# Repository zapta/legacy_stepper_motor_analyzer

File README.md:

# Legacy Stepper Motor Analyzer

<span style="color:red"><b>
NOTE: This is the legacy STM32 based design which was  replaced by the single board, Raspberry Pi Pico design at https://github.com/zapta/simple_stepper_motor_analyzer.</b></span>

&nbsp;

https://github.com/zapta/legacy_stepper_motor_analyzer

&nbsp;

&nbsp;

## Demonstration

Michael from the Teaching Tech youtube channel made [a great video explaining how stepper motors work](https://youtu.be/4iII25DGIdA) and used the Simple Stepper Motor Analyzer for some of the demonstrations. 

&nbsp;

## Highlights
* Low cost and minimalist DYI hardware design.
* Standalone. Doesn't require a computer to operate.
* Analyzes the stepper motor signals in the actual system (e.g. a 3D printer).
* Galvanically isolated current sensors. Does not interfere with the operating equipment, even when its turned off.
* Easy to connect using a pair 4 wire pass through connectors.
* Intuitive user interface with color display and a capacitive touch.
* Microstepping resolution of 1% of a full step.
* Provides momentary readings, signal patterns, and statistical measurements.
* Hardware and software are open sourced with a generous license.
* Based on free tools (Kicad, platformio, LVGL, STM32Duino).
* Can be easily customized (new featured, cost reduction, data link to a computer, etc).
* Powered 5VDC, 200ma via a USB-C connector.

## Overview
Diagnosing the operation of stepper motor in 3D printers and CNC machines used to require stepper motor analyzers that costs thousands of dollar. Not anymore! The Simple Stepper Analyzer ('Analyzer' in short) brings these capabilities to every maker for a tiny fraction of the price and with a minimalist DIY electronic design that leaves the heavy lifting to the firmware.

The Analyzer is self contained, has two 4-wires pass-through connectors connecting the stepper motor, is powered from a common 5V charger with a micro USB cable, provides a simple to use graphical user interface with a 3.5" color touch screen, and provides a plethora of stepper motor measurements.

The Analyzer is provided to the community as a public domain reference design that can be built and used as is, or be customized with additional features or for a lower cost as desired. The hardware and firmware come with a liberal open source license (CC0) that allows commercial usages and doesn't require code source code sharing.

---
## Disclaimer
THE DESIGN IS PROVIDED "AS IS", WITHOUT WARRANTY OF ANY KIND, EXPRESS OR IMPLIED, INCLUDING BUT NOT LIMITED TO THE WARRANTIES OF MERCHANTABILITY, FITNESS FOR A PARTICULAR PURPOSE AND NONINFRINGEMENT. IN NO EVENT SHALL THE AUTHORS OR COPYRIGHT HOLDERS BE LIABLE FOR ANY CLAIM, DAMAGES OR OTHER LIABILITY, WHETHER IN AN ACTION OF CONTRACT, TORT OR OTHERWISE, ARISING FROM, OUT OF OR IN CONNECTION WITH THE DESIGN OR THE USE OR OTHER DEALINGS IN THE DESIGN.

---

## Alternative construction option (enclosed case)
**NOTE:** This pages outlines the open base construction options which is easier and straight forward. For a more involved and potentially more satisfying construction option, which is also featured in the Teaching Tech youtube video, see https://github.com/zapta/legacy_stepper_motor_analyzer/blob/master/case_option.md

---
## How does it work?
The principle of operation is very simple, and so is the hardware design. The stepper motor is connected via 4 wire pass-though connectors that allow the Analyzer to monitor the current through the stepper's coils. The Analyzer's user low impedance current sensors that are galvanically isolated such does not interfere with the operation of the 3D printer or other equipment it monitors. The Analyzer measures the coils currents 100k times a second and uses firmware that analyzes the data, extracts the desired measurements, and present them on the screen. For example, this is how an analysis of the distribution of distance by speed distribution looks like:

---
## Operation is simple and intuitive

1. Turn off power to the equipment (e.g. 3D printer).
2. Disconnect the 4 wires of the stepper motor and connect them through the Analyzer two pass through connectors.
3. Power the analyzer using a 5V charger and a micro USB cable.
4. Turn on the equipment and get the stepper going.
5. Use the Analyzer's screen to view the measurements you want.

**NOTE:** The two pass-through connectors of the Analyzer are symmetric and  each can act as an input or output. 

**CAUTION:** Always connect and disconnect stepper motors when their controller is not energized, to reduce the risk of damage to the controller due to high voltage spikes. The analyser itself is not subject to that risk since its uses galvanically isolated current sensors.

**NOTE:** The only requirement for proper wiring is that the two wires of one coil should go through pins pair 1,2 and the two wires of the other coil should go through pin pair 3,4. The Analyzer doesn't care about the +/- polarity of the wires in each pair, nor does it care which of the two pass-through connectors is on the controller side and which one is on the stepper side.

**TRIVIA:**: The pin out and the connector type of the Analyzer follows the Duet3D conventions, except that is uses right angle connector to save space.

---
## The Home Page
The Home page is first page shown when the Analyzer is powered on. It provides summary information as well as access to the Settings page.

&nbsp;

#### Page Data

Field | Description
:------------ | :-------------
 COIL&nbsp;1 | Momentary coil 1 current in Amps.
 COIL&nbsp;2 | Momentary coil 2 current in Amps.
 ERRORS | The number of phase errors detected so far. Phase errors happens when the current patterns are so distorted that a forward/backward movement cannot be determined.
 POWER | Indicates if the stepper motor is currently energized. This is determined by the sum of currents in they two coils.
 IDLES | The number of times that stepper motor change status from energized to non energized.
 STEPS | The distance the stepper moved so far. Each full step forward increments this value by one and each full step backward decrements it by one. When the stepper motor is energized, the display also shows fractional steps in resolution of 1/100th of a full step.

HINT: The fractional step value cannot be reset because it is derived from the momentary currents in the two coils. Only the stepper motor driver can reset the fraction by positioning the stepper motor on an exact full step.

HINT: To swap forward/backward directions of the Analyzer use the Settings page. This does not affect the stepper motor itself.

&nbsp;
#### Page Actions

Action | Description
:------------: | :-------------
 | Clear all data.
 | Open the Settings page.

&nbsp;

---

## The Settings Page

This is a special page that is accessible from the Home page and allows to calibrate the Analyzer. The settings are stored in a non volatile memory and are preserved when the Analyzer is turned off.

&nbsp;
#### Page Data

Data | Description
:------------: | :-------------
COIL&nbsp;1 | The momentary current of stepper coil 1 in Amp units. Should be zero, or very close to zero, when the stepper motor is disconnected.
COIL&nbsp;2 | The momentary current of stepper coil 2 in Amp units. Should be zero, or very close to zero, when the stepper motor is disconnected.

&nbsp;
#### Page Actions

Action | Description
:------------: | :-------------
SET ZERO | Used to calibrate the zero reading of the current sensors. To do so, Disconnect the stepper motor and press this button.
REVERSE STEPS DIRECTION | Changes the forward/backward step directions of the Analyzer. Does not affect the stepper motor itself. Having the correct direction is important for measurements such as the Retraction analysis.
 | Press exist the Settings page.

&nbsp;

---

## The Speed Dial Page

This page measure the stepper speed in units of full steps per second. 

&nbsp;
#### Page Data

Data | Description
:------------ | :-------------
Speed&nbsp;Dial | The speed dial shows the momentary stepper speed in full steps per second units. Forward speed is on the right side and backward speed is on the left.
Speed&nbsp;Value | This field shows the speed in a numeric form. IT is updated less frequently than the dial to allow easy reading.

&nbsp;
**HINT:** The Settings page allows to swap the forward/backward directions.

&nbsp;
#### Page Actions

Action | Description
:------------: | :-------------
 | Clears all data.
Tap the dial |Toggles the dial's speed range.

&nbsp;

---

## The Distance Graph Page

This page shows scrolling graph with the total number of full steps vs. time.

&nbsp;

#### Page Data

Data | Description
:------------ | :-------------
Distance&nbsp;Graph | This graph shows how the distance, in units of full steps, changes over time.
Distance&nbsp;value | The numeric value of the distance in full steps.  This fields is identical to the STEPS field in the Home page.

&nbsp;

#### Page Actions

Action | Description
:------------: | :-------------
 | Clears all data.
Tap the graph | Toggles the range of the vertical axis.

&nbsp;

---

#### The Retraction Graph Page

This page is useful to analyze the retraction in of 3D printer extruder.

&nbsp;
**TRIVIA:** The graph above was taken while testing a direct extruder printer with [Thing #909901](https://www.thingiverse.com/thing:909901).
&nbsp;
#### Page Data

Data | Description
:------------ | :-------------
Retraction&nbsp;Graph | This graphs tracks the retraction of 3D extruder full step units.  Retraction is defined as the filament length that was inside the extruder and is now retracted outside of the extruder. 
Retraction value |  This field shows the current retraction level in a numeric form.

&nbsp;
#### Page Actions

Action | Description
:------------: | :-------------
 | Clear all data.
Tap the graph | Changes the range of the vertical axis.

&nbsp;

---

## The Time by Speed Page

This page shows an histogram with the distributing of time by stepper speed. That is how much time was spent in each speed range. The values are normalized such that the longest bar is always at 100%.

&nbsp;
#### Page Data

Data | Description
:------------ | :-------------
Time&nbsp;Histogram | The horizontal axis indicates speed in full steps per second units. The height of each bar indicate the time of all steps in that speed range, with the length of the longest bar normalized to 100%.

&nbsp;
#### Page Actions

Action | Description
:------------: | :-------------
 | Clear all data.

&nbsp;

---

## The Distance by Speed Page

This page shows an histogram with the the distribution of distance by stepper speed.

&nbsp;
#### Page Data

Data | Description
:------------ | :-------------
Distance&nbsp;Histogram |  The horizontal axis indicates speed in full steps per second units. The height of each bar indicate the distance or number of steps in that speed range, with the length of the longest bar normalized to 100%.

&nbsp;
#### Page Actions

Action | Description
:------------: | :-------------
 | Clear all data.

&nbsp;

---

## The Current by Speed Page

This page measures the ability of the stepper motor's controller to maintain peak current at high speeds.

The screenshot below shows a healthy system where the peak current is virtually flat across the speed range.

The screenshot below shows a system that is not capable to maintain peak current and starves the stepper motor at high speeds, resulting in poor torque and possible skipped steps.

&nbsp;
#### Page Data

Data | Description
:------------ | :-------------
Peak&nbsp;Current&nbsp;Histogram | The horizontal axis indicates speed in full steps per second units. The height of each bar indicates the average peak current in Amps of  steps that speed range. 

&nbsp;
#### Page Actions

Action | Description
:------------: | :-------------
 | Clear all data.

&nbsp;

---

## Coil Current Patterns Page

This page shows the current patterns in the two stepper coils.

The screenshot below shows a healthy system where the signals are nice and clean and reaches the target peak current.

&nbsp;

The screenshot below is from a poor system where high speed results in distorted and insufficient current, resulting in loss of torque and a potential for skipped steps.

&nbsp;

**GENERAL INFORMATION:** Each cycle of the stepper current pattern represent 4 full steps. The centers of those steps are at on the four vertical dotted lines where the currents of the two coils are identical, in the same or in  opposite polarities. The transitions between the steps are on the 4 vertical solid lines where one of the coils is at zero current. This cycle of 4 full steps is sometimes referred to as a single 'electric rotation'. The analyzer computes the exact phase on this cycle using the standard trigonometric function atan2(current1, current2) which can also be calculated manually from the current readings in the Home page.

&nbsp;

#### Page Data

Data | Description
:------------ | :-------------
Current&nbsp;graph | The horizontal axis indicates time in milliseconds. The vertical axis indicate coil current level in Amps. The two graphs show the current patterns of the respective stepper coils.

**NOTE:** The graph is updated only when sufficient stepper motor movement is detected.

&nbsp;
#### Page Actions

Action | Description
:------------: | :-------------
 | Clear all data.
 | When running, pauses the display updates.
 | When paused, resume the display updates.
Tap the graph | This toggles the range of the horizontal axis.

&nbsp;

---

## Coil Current Phase Page

This page draws the current patterns of the two coils as a [Lissajous curve](https://en.wikipedia.org/wiki/Lissajous_curve) which allows to examine visually distortions such as non sinusoidal current, phase distortion, and reduced amplitude.

In an ideal system, the graph is a perfect smooth circle, that doesn't change its size when the stepper's speed changes. Patterns that significantly diverge from that indicates a sub optimal configuration and operation.

Following picture shows a pattern from a well functioning system. The graph is round, reasonable smooth, and has sufficient size which indicates good current drive. 

The horizontal axis indicates the coil 1 current and the vertical axis indicates coil 2 current. In this example, both span nicely between -2A to +2A.

&nbsp;

The screenshot below is from a poor system where high speed results in distorted and insufficient current, resulting in loss of torque and a potential for skipped steps. The pattern is far from a clean circle and the shape has reduced size.

&nbsp;

The screenshot below shows a sub optimal operation where a a speed increase of the stepper results in small (less current and torque) and even more distorted curve.

&nbsp;

The screenshot below shows a well functioning system. The smaller size of the circle compare to the example above indicates that it operates on lower current.

&nbsp;

The screenshot below show an operation of a stepper in full steps mode. The dimension of the pattern indicate good current feed, and the square  shape is the best a full step driver can deliver.

&nbsp;

The screenshot below show an operation of a stepper in half steps mode. The dimension of the pattern indicate good current feed, and the shape is somewhere between the square shape of full step mode and the round shape of micro stepping interpolation mode.

&nbsp;

#### Page Data

Data | Description
:------------ | :-------------
Lissajous&nbsp;curve | A Lissajous curve drawn from the current pattern of coil 1 (x) and coil2(y). 
Capture speed | Shows the signal capture time. Fast mode works better with fast moving steppers and slow mode works with slow moving steppers. Tap the graph to toggle.

**NOTES** 
* The graph is updated only when sufficient stepper motor movement is detected.
* To view the current pattern that resulted in the current phase pattern, use the navigation button to switch the current patters page, and vice versa.

&nbsp;
#### Page Actions

Action | Description
:------------: | :-------------
 | Clear all data.
 | When running, pauses the display updates.
 | When paused, resume the display updates.
Tap the graph | This toggles the capture time between fast and slow speeds.

&nbsp;

---

## Reference Design Specification

Item | Specification
:------------ | :------------- 
Power consumption | 5V, 175ma.
Power connector | micro USB
MCU | 32bit ARM STM32F401CE @ 84Mhz.
Flashing | USB/DFU or SWD/Stlink V2.
Data link | USB/Serial link available but not used.
Current measurement | +/-2.5A per coil. +/-5A sensors available.
Dimensions | 97 x 66 mm
TFT Resolution | 480 x 320, Color. Landscape mode.
Touch screen | Capacitive
Sensor isolation | See ACS70331 data sheet
Sampling rate | 100Khz per channel.
Sampling resolution | 12bits
Current accuracy | estimated at +/- 1%
Max speed | Software dependent. Currently 2K full steps/sec.
Step resolution | 1/100th of a full step.
Partial steps measurement | Software dependent. Not implemented.
Settings storage | On board EEPROM chip.
GUI framework | LVGL library. R3G3B2 color depth.
Programming language | C++
Programming IDE | Platform.io. Arduino/STM32.
Cad package | Kicad.

&nbsp;

---

## I want to build me one

The electronic schematic, PCB layout, gerber files, and the firmware source files and released binary are all available on this github repository.

[Schematic](./www/stepper_analyzer-sch.pdf)

[BOM](https://github.com/zapta/legacy_stepper_motor_analyzer/blob/master/kicad/BOM.csv)

<span style="color:red"><b>
ERRATA: The current PCB version leaves the RD input on the TFT (pin 26) floating which can  interfere with the operation of the display. One workaround is to patch the board with a resistor to pull the input to +3.3v (but not to +5V!!!). See the errata in the latest schematic for more details.</b></span>

&nbsp;

**Instructions:** Build the PCB, use DFU or SWD protocols to program the released binary into the Blackpill, plugin the TFT screen, power and use. See instructions below on how to flash the firmware release you can find on this github repository.

**NOTE:** These instructions are for the simpler  version which uses an open frame base. For ordering parts and building the enclosed version see https://github.com/zapta/legacy_stepper_motor_analyzer/blob/master/case_option.md .

&nbsp;

## Flashing a new firmware
Flashing the Analyzer with firmware can be done in a few ways. For software developers we recommend using StLink V2 and SWD which are well supported by the platformio IDE and enable debugging ans single stepping. A simpler approach that is recommended for end users is to use the builtin DFU protocol of the Analyzer's STM32 processor such as the one we use here. Adafruit has a [good description of the process](https://learn.adafruit.com/adafruit-stm32f405-feather-express/dfu-bootloader-details). The only difference that to enable the DFU bootloader mode connect the analyzer to the computer while its BOOT0 on button on the back is pressed.

**ONLINE LOADER:** We also had good results with Google Chrome browser and this online loader https://devanlai.github.io/webdfu/dfu-util/ . The Analyzer should appear as STM32 BOOTLOADER and should be programmed with the configuration Internal Flash 0x08000000.

## How to modify the firmware?
The source code of the Analyzer is available on this github repository. It is a STM32 C++ Platformio project that uses the Arduino framework. The user interface is based on the LVGL library and the project includes its own port to support TFT/Touch used.  Knowledge of C++ and Platformio is required and is outside the scope of this document.

## Mechanical
We provide here a [3D model of a simple open frame carrier](./3d/base.stl). This design does not requires attaching the analyzer and the TFT board with screws or spacers and guarantees proper separation on the loose end. If you have an interesting design which you would like to share, please post in a model sharing site such as cults3d, thingiverse or grabcad and we will link it here.

This open frame base does not require any spacers between the two boards and was designed 
to prevent them from unintentionally touching each other.

## Ideas for improvements
The Analyzer is provided as a fully functional reference design and changes and the developers encourage improvement/modifications of the hardware and/or firmware are encouraged. This can include new features, new measurements and pages, extending the design to support 2 or 3 steppers at once to track the x/y/z of a 3D printer, reducing the hardware cost using less expensive screen TFT, or even eliminating the screen altogether and using the Analyzer as a dongle tethered to a computer via the existing USB/Serial link.

&nbsp;

---

## FAQ

#### Q: Why not a SPI based TFT?

A: We could not achieve fast enough display refresh rate with SPI so switched to 16 bit parallel data transfers.

#### Q: Can a cheaper TFT/touch be used?
A: Yes, but it may require firmware changes.

#### Q: Can the TFT screen be eliminated?
A: Yes. The Analyzer has a USB/Serial output can a small Analyzer dongle can communicate with a computer program. This will require firmware changes.
 
#### Q: Can I connect the Analyzer to the TFT using a FFC cable?

A: Yes. The PCB was designed for both 0.1" header and 40 pins 1.0mm FFC cable connections.  You will need a short (e.g. 60mm or less) type B ('reversed') FFC cable. Cables longer than let's say 100mm may introduce noises the will interfere with the operation of the display. 

#### Q: Can you add feature X or customization Y?

A: Most likely not. The reference design is provided for the community to change and mix.

#### Q: I want to commercialize or crowd source it, can you help me?

A: Most likely not. The reference design is open source and you will need to find others to help you.

#### Q: Where do I file a bug?

A: Use the github repository.

#### Q: Is it ok to connect/disconnect power to the Analyzer while my 3D printer prints?

A: Of course. The Analyzer is isolated from the stepper wires and should not interfere with the operation of the printer.

#### Q: The Analyzer uses LVGL lib, what is the license of that library?

A: At the time of writing this, the LVGL license is available here https://github.com/lvgl/lvgl/blob/master/LICENCE.txt.  The Analyzer's developers are not affiliated with LVGL.

#### Q: Is the LVGL library included in the Analyzer's repository?

A: It's not needed. LVGL is supported by platform.io so the Analyzer's project is set for platform.io to fetch LVGL automatically.

#### Q: Can I use a STM32F401CE MCU with a 8Mhz crystal.

A: The provided firmware assumes a 25Mhz crystal. For a 8Mhz crystal you will need to change the firmware.

#### Q: I can't find a STM32F401CE/25Mhz blackpill but I can find an STM32F411CE/25Mhz, will this work?

A: Most like it will work with the provided firmware as is (and with no performance benefits), but we do not guarantee it. We may switch the official reference design to the STMF411CE/25Mhz if the STM32F401CE/25Mhz, which is less expensive, will not be available.

#### Q: Can I use a blackpill with different pinout than WeAct ?

A: No, unless if you are willing to change the PCB.

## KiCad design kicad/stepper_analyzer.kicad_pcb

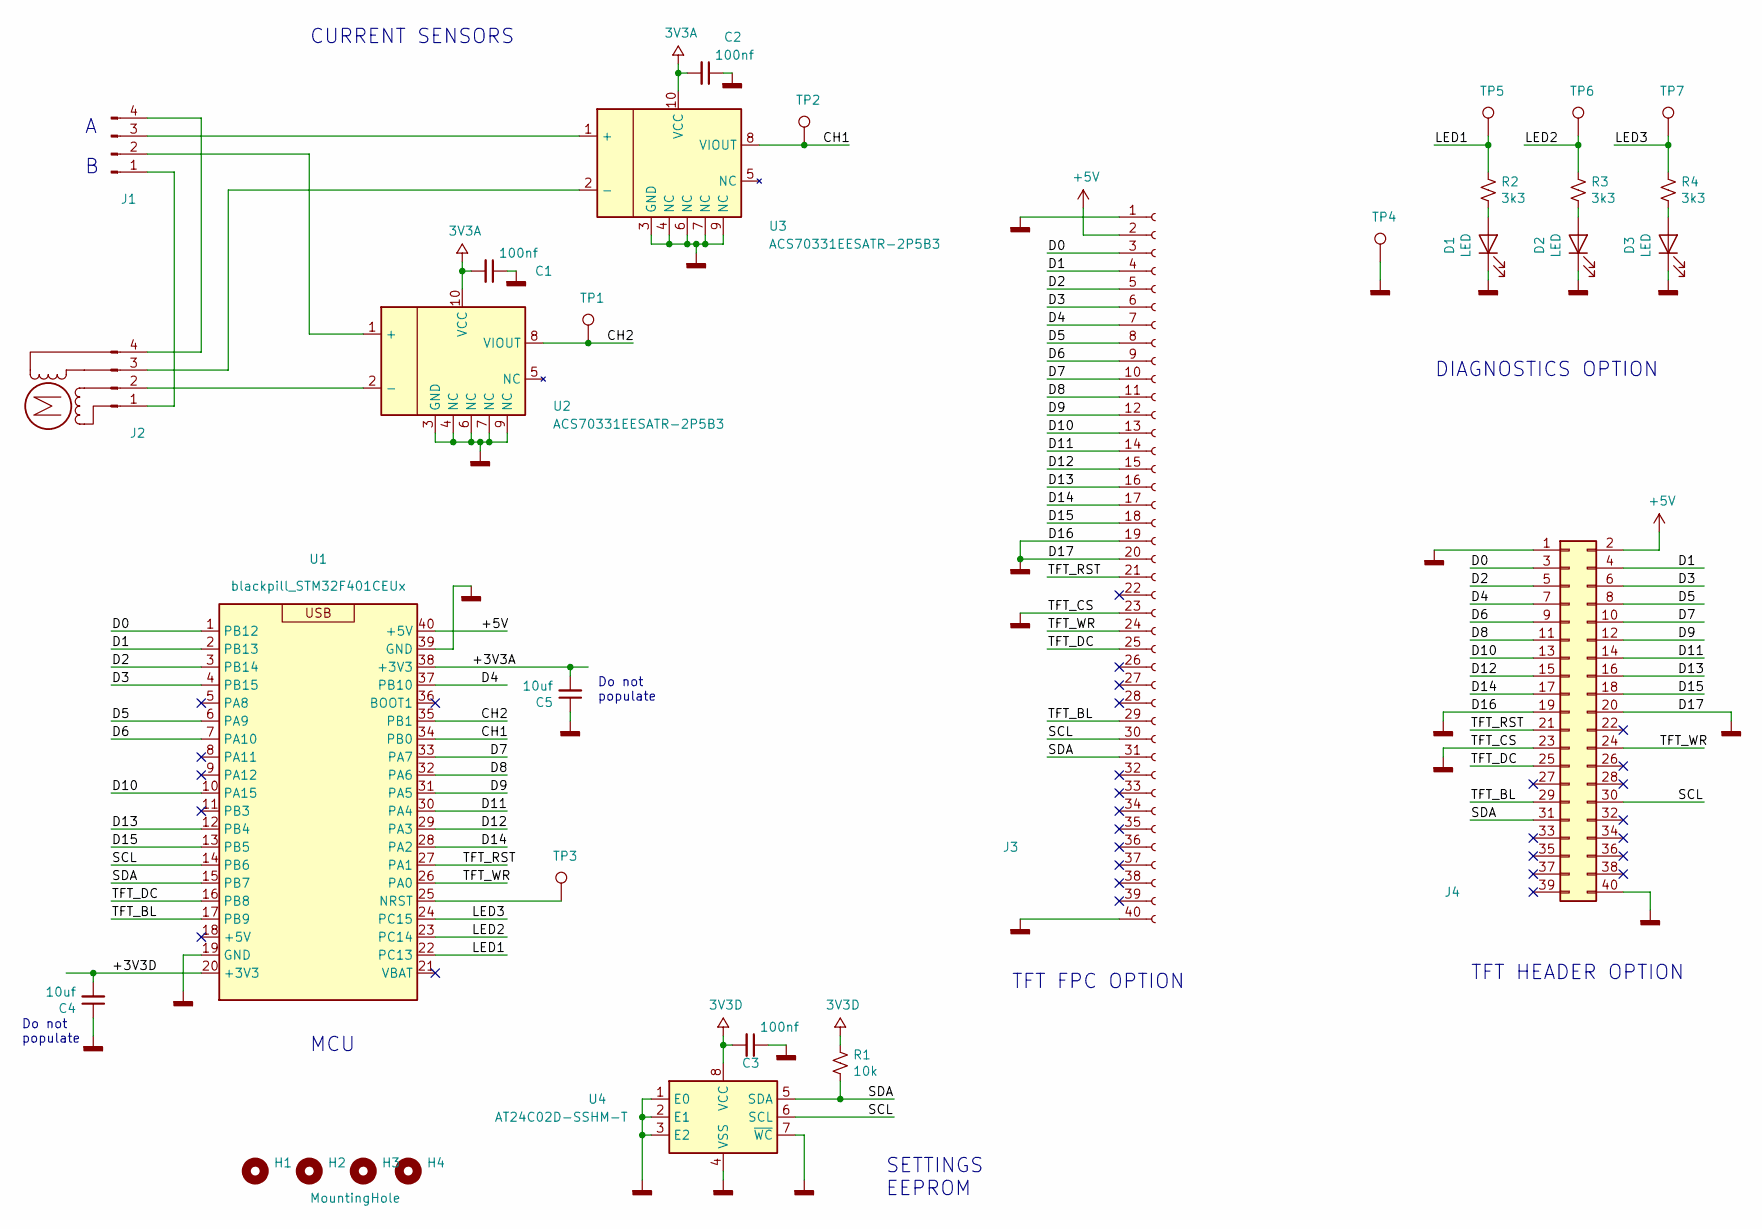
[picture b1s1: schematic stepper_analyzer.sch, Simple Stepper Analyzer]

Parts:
C1, C2, C3: 100nf; C_0603_1608Metric_Pad1.08x0.95mm_HandSolder
C4, C5: 10uf; C_0603_1608Metric_Pad1.08x0.95mm_HandSolder
D1, D2, D3: LED; LED_0603_1608Metric_Pad1.05x0.95mm_HandSolder
H1, H2, H3, H4: MountingHole
J1, J2: Conn_01x04_Male; connector_4pins_horizontal
J3: Conn_01x40_Female; FPC_connector_40P_1.0mm
J4: Conn_02x20_Odd_Even; PinSocket_2x20_P2.54mm_Vertical
M1: Stepper_Motor_bipolar; null_footprint
R1: 10k; R_0603_1608Metric_Pad1.05x0.95mm_HandSolder
R2, R3, R4: 3k3; R_0603_1608Metric_Pad1.05x0.95mm_HandSolder
TP1, TP2, TP3, TP4, TP5, TP6, TP7: TestPoint; testpoint
U1: blackpill_STM32F401CEUx; blackpill_module
U2, U3: ACS70331EESATR-2P5B3; Allegro_QFN-12-10-1EP_3x3mm_P0.5mm
U4: AT24C02D-SSHM-T; SOIC-8_3.9x4.9mm_P1.27mm

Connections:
+5V: J3.2, J4.2, U1.40 (+5V)
/CH1: TP2.1, U1.34 (PB0), U3.8 (VIOUT)
/CH2: TP1.1, U1.35 (PB1), U2.8 (VIOUT)
/D0: J3.3, J4.3, U1.1 (PB12)
/D1: J3.4, J4.4, U1.2 (PB13)
/D2: J3.5, J4.5, U1.3 (PB14)
/D3: J3.6, J4.6, U1.4 (PB15)
/D4: J3.7, J4.7, U1.37 (PB10)
/D5: J3.8, J4.8, U1.6 (PA9)
/D6: J3.9, J4.9, U1.7 (PA10)
/D7: J3.10, J4.10, U1.33 (PA7)
/D8: J3.11, J4.11, U1.32 (PA6)
/D9: J3.12, J4.12, U1.31 (PA5)
/D10: J3.13, J4.13, U1.10 (PA15)
/D11: J3.14, J4.14, U1.30 (PA4)
/D12: J3.15, J4.15, U1.29 (PA3)
/D13: J3.16, J4.16, U1.12 (PB4)
/D14: J3.17, J4.17, U1.28 (PA2)
/D15: J3.18, J4.18, U1.13 (PB5)
/LED1: R2.1, TP5.1, U1.22 (PC13)
/LED2: R3.1, TP6.1, U1.23 (PC14)
/LED3: R4.1, TP7.1, U1.24 (PC15)
/SCL: J3.30, J4.30, U1.14 (PB6), U4.6 (SCL)
/SDA: J3.31, J4.31, R1.2, U1.15 (PB7), U4.5 (SDA)
/TFT_BL: J3.29, J4.29, U1.17 (PB9)
/TFT_DC: J3.25, J4.25, U1.16 (PB8)
/TFT_RST: J3.21, J4.21, U1.27 (PA1)
/TFT_WR: J3.24, J4.24, U1.26 (PA0)
GNDD: C1.1, C2.1, C3.1, C4.1, C5.1, D1.1 (K), D2.1 (K), D3.1 (K), J3.1, J3.19, J3.20, J3.23, J3.40, J4.1, J4.19, J4.20, J4.23, J4.40, TP4.1, U1.19 (GND), U1.39 (GND), U2.3 (GND), U2.4 (NC), U2.6 (NC), U2.7 (NC), U2.9 (NC), U3.3 (GND), U3.4 (NC), U3.6 (NC), U3.7 (NC), U3.9 (NC), U4.1 (E0), U4.2 (E1), U4.3 (E2), U4.4 (VSS), U4.7 (~WC)
unnamed: D1.2 (A), R2.2
unnamed: D2.2 (A), R3.2
unnamed: D3.2 (A), R4.2
unnamed: J1.1, J2.1
unnamed: J1.2, U2.1 (+)
unnamed: J1.3, U3.1 (+)
unnamed: J1.4, J2.4
unnamed: J2.2, U2.2 (-)
unnamed: J2.3, U3.2 (-)
unnamed: TP3.1, U1.25 (NRST)

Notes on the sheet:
MCU
SETTINGS EEPROM
CURRENT SENSORS
TFT HEADER OPTION
TFT FPC OPTION
DIAGNOSTICS OPTION
Do not populate

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
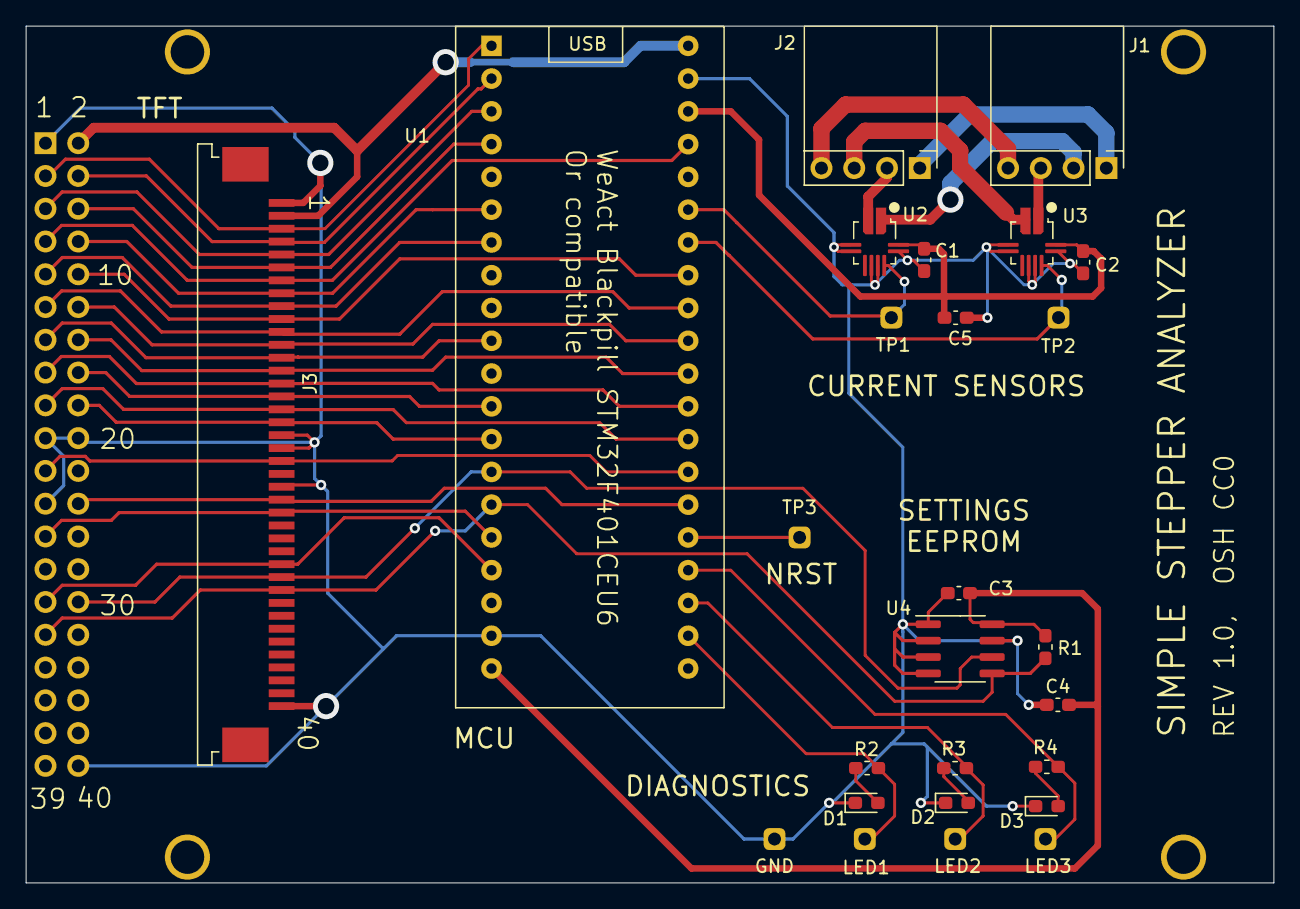
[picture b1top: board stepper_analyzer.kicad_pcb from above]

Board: 2 copper layers, 96.7 x 66.4 mm, 32 parts (1 on the bottom side), 41 nets.

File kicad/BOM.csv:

Quantity,Ref, Value,Status, Description,Source,Comments
3,"C1, C2, C3",100nf,Required,"Ceramic capacitor 100nf, at least 10V, SMD 0603",Digikey 311-1369-1-ND,"Generic component, available from other  sources."
2,"C4, C5",10uf,Requires,"Ceramic capacitor 10uf, at least 10V, SMD 0603",Digikey311-1817-1-ND,"Generic component, available from other  sources."
1,R1,10k,Required,"Chip resistor 10k, SMD 0603",Digikey 13-AC0603FR-0711KLCT-ND,"Generic component, available from other  sources."
2,"J1, J2",4 pins right angle connector,Required,KF2510 male connector right angle 0.1 pitch pin header,https://www.aliexpress.com/item/4000587555738.html,"Generic component, available from other  sources."
1,J4,2x20 0.1 female header. ,Required,Connector_PinSocket_2.54mm:PinSocket_2x20_P2.54mm_Vertical,https://www.aliexpress.com/item/32747224548.html,"Generic component, available from other  sources."
1,U1,WeAct STM32F4x1CE blackpill module.,Required,WeAct blackpill STM32F401CE 25Mhz or STM32F411CE.  Comes  with 2x20 pin headers to solder the blackpill to the analyzers PCB.,https://www.aliexpress.com/item/1005001456186625.html,"Some clones of WeAct modules are available. Make sure to have the same pinout and legit MCU.  STM32401CC wouldnt work, also, make sure it has 25Mhz crystal (vs 8Mhz)."
2,"U2, U3",ACS70331EESATR-2P5B3,Required,"Alegro current sensor, bidirectional, +/-2.5A.
",Digikey 620-1889-1-ND,
1,U4,AT24C02D-SSHM-T,Required,I2C EEPROM 256x8,Digikey AT24C02D-SSHM-TCT-ND,Clones are available on Aliexpress. We didnt test them but should work as well.
1,,Analyzer PCB Rev 1.0,Required,Gerber files are available the github repository.  96.7 x 66.4mm two layers.,"JLCPCB, Pcbway, your prefer PCB vendor or shop at https://pcbshopper.com/",
1,,BuyDisplay 3.5 TFT with touch display ,Required,"ER-TFTM035-6, Pin Header Connection-8080 16-bit Parallel, 5.0V, Capacitive Touch Panel, No font chip.",https://www.buydisplay.com/lcd-3-5-inch-320x480-tft-display-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,Make sure to select the exact options listed in the Description column. See example at https://github.com/zapta/simple_stepper_motor_analyzer/blob/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
3,"D1, D2, D3",LED 0603.,"Optional, for firmware development only.","LED SMD 0603, colors of your choice.",https://www.aliexpress.com/item/32888575577.html,"Generic component, available from other  sources."
3,"R2,R3, R4",3k3,"Optional, for firmware development only.","Chip resistor 3.3k, SMD 0603",Digikey YAG3354CT-ND,"Generic component, available from other  sources."
1,,STLINK V2,"Optional, for firmware development only.",Hardware debugger for STM32 MCUs.,"Digikey  497-10484-ND
",Inexpensive USB dongle clones are available from Aliexpress. We expect them to work but didnt test them.

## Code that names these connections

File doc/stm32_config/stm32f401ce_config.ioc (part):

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Mcu.Name=STM32F401C(D-E)Ux
Mcu.Package=UFQFPN48
Mcu.UserName=STM32F401CEUx
PA0-WKUP.GPIOParameters=GPIO_Speed,GPIO_Label
PA0-WKUP.GPIO_Label=TFT_WR
PA0-WKUP.GPIO_Speed=GPIO_SPEED_FREQ_VERY_HIGH
PA0-WKUP.Signal=GPIO_Output
PA1.GPIOParameters=GPIO_Speed,GPIO_Label
PA1.GPIO_Label=TFT_RST
PA1.GPIO_Speed=GPIO_SPEED_FREQ_VERY_HIGH
PA1.Signal=GPIO_Output
PA10.GPIOParameters=GPIO_Label
PA10.GPIO_Label=TFT_D6
PA10.Signal=GPIO_Output
PA11.Mode=Device_Only
PA11.Signal=USB_OTG_FS_DM
PA12.Mode=Device_Only
PA12.Signal=USB_OTG_FS_DP
PA13.Mode=Trace_Asynchronous_SW
PA13.Signal=SYS_JTMS-SWDIO
PA14.Mode=Trace_Asynchronous_SW
PA14.Signal=SYS_JTCK-SWCLK
PA15.GPIOParameters=GPIO_Speed,GPIO_Label
PA15.GPIO_Label=TFT_D10               
PA15.GPIO_Speed=GPIO_SPEED_FREQ_VERY_HIGH
PA15.Signal=GPIO_Output
PA2.GPIOParameters=GPIO_Speed,GPIO_Label
PA2.GPIO_Label=TFT_D14
PA2.GPIO_Speed=GPIO_SPEED_FREQ_VERY_HIGH
PA2.Signal=GPIO_Output
PA3.GPIOParameters=GPIO_Speed,GPIO_Label
PA3.GPIO_Label=TFT_D12
PA3.GPIO_Speed=GPIO_SPEED_FREQ_VERY_HIGH
PA3.Signal=GPIO_Output
PA4.GPIOParameters=GPIO_Speed,GPIO_Label
PA4.GPIO_Label=TFT_D11
PA4.GPIO_Speed=GPIO_SPEED_FREQ_VERY_HIGH
PA4.Signal=GPIO_Output
PA5.GPIOParameters=GPIO_Speed,GPIO_Label
PA5.GPIO_Label=TFT_D9
PA5.GPIO_Speed=GPIO_SPEED_FREQ_VERY_HIGH
PA5.Signal=GPIO_Output
PA6.GPIOParameters=GPIO_Speed,GPIO_Label
PA6.GPIO_Label=TFT_D8
PA6.GPIO_Speed=GPIO_SPEED_FREQ_VERY_HIGH
PA6.Signal=GPIO_Output
PA7.GPIOParameters=GPIO_Speed,GPIO_Label
PA7.GPIO_Label=TFT_D7
PA7.GPIO_Speed=GPIO_SPEED_FREQ_VERY_HIGH
PA7.Signal=GPIO_Output
PA8.Signal=S_TIM1_CH1
PA9.GPIOParameters=GPIO_Speed,GPIO_Label
PA9.GPIO_Label=TFT_D5
PA9.GPIO_Speed=GPIO_SPEED_FREQ_VERY_HIGH
PA9.Signal=GPIO_Output
PB0.GPIOParameters=GPIO_Label
PB0.GPIO_Label=AIN0
PB0.Signal=ADCx_IN8
PB1.GPIOParameters=GPIO_Label
PB1.GPIO_Label=AIN1
PB1.Signal=ADCx_IN9
PB10.GPIOParameters=GPIO_Speed,GPIO_Label
PB10.GPIO_Label=TFT_D4
PB10.GPIO_Speed=GPIO_SPEED_FREQ_VERY_HIGH
PB10.Signal=GPIO_Output
PB12.GPIOParameters=GPIO_Speed,GPIO_Label
PB12.GPIO_Label=TFT_D0
PB12.GPIO_Speed=GPIO_SPEED_FREQ_VERY_HIGH
PB12.Signal=GPIO_Output
PB13.GPIOParameters=GPIO_Speed,GPIO_Label
PB13.GPIO_Label=TFT_D1
PB13.GPIO_Speed=GPIO_SPEED_FREQ_VERY_HIGH
PB13.Signal=GPIO_Output
PB14.GPIOParameters=GPIO_Speed,GPIO_Label
PB14.GPIO_Label=TFT_D2
PB14.GPIO_Speed=GPIO_SPEED_FREQ_VERY_HIGH
PB14.Signal=GPIO_Output
PB15.GPIOParameters=GPIO_Speed,GPIO_Label
PB15.GPIO_Label=TFT_D3
PB15.GPIO_Speed=GPIO_SPEED_FREQ_VERY_HIGH
PB15.Signal=GPIO_Output
PB3.Mode=Trace_Asynchronous_SW
PB3.Signal=SYS_JTDO-SWO
PB4.GPIOParameters=GPIO_Speed,PinState,GPIO_Label
PB4.GPIO_Label=TFT_D13
PB4.GPIO_Speed=GPIO_SPEED_FREQ_VERY_HIGH
PB4.PinState=GPIO_PIN_RESET
PB4.Signal=GPIO_Output
PB5.GPIOParameters=GPIO_Speed,GPIO_Label
PB5.GPIO_Label=TFT_D15
PB5.GPIO_Speed=GPIO_SPEED_FREQ_VERY_HIGH
PB5.Signal=GPIO_Output
PB6.Mode=I2C
PB6.Signal=I2C1_SCL
PB7.Mode=I2C
PB7.Signal=I2C1_SDA
PB8.GPIOParameters=GPIO_Speed,GPIO_Label
PB8.GPIO_Label=TFT_DC
PB8.GPIO_Speed=GPIO_SPEED_FREQ_VERY_HIGH
PB8.Signal=GPIO_Output
PB9.GPIOParameters=GPIO_Speed,GPIO_Label
PB9.GPIO_Label=TFT_BL
PB9.GPIO_Speed=GPIO_SPEED_FREQ_VERY_HIGH
PB9.Signal=GPIO_Output
PC13-ANTI_TAMP.GPIOParameters=GPIO_Label
PC13-ANTI_TAMP.GPIO_Label=LED1
PC13-ANTI_TAMP.Signal=GPIO_Output
PC14-OSC32_IN.GPIOParameters=GPIO_Label
PC14-OSC32_IN.GPIO_Label=LED2
PC14-OSC32_IN.Signal=GPIO_Output
PC15-OSC32_OUT.GPIOParameters=GPIO_Label
PC15-OSC32_OUT.GPIO_Label=LED3
PC15-OSC32_OUT.Signal=GPIO_Output
PH0\ -\ OSC_IN.Mode=HSE-External-Oscillator
PH0\ -\ OSC_IN.Signal=RCC_OSC_IN
PH1\ -\ OSC_OUT.Mode=HSE-External-Oscillator
PH1\ -\ OSC_OUT.Signal=RCC_OSC_OUT
RCC.HSE_VALUE=25000000
RCC.SYSCLKFreq_VALUE=84000000
RCC.SYSCLKSource=RCC_SYSCLKSOURCE_PLLCLK
board=custom

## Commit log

2021-01-30 Created repository
2021-01-30 Added board images
2021-01-30 Fixed a typo
2021-01-30 Updated documentation
2021-01-30 Updated 3D model
2021-01-31 Reduce annoyance from blinking LED3 and added a dated binary release.
2021-02-01 Flushing cleanup of quadrant model.
2021-02-02 Added analysis of fractional steps.
2021-02-07 Doubled the pixels transfer rate from 5M pix/sec to 10 by flatening the render loop, merging porta/b bssr table and caching the color table in RAM.
2021-02-07 Added a comment.
2021-02-09 Removed commented out code.
2021-02-10 Added a function to create polar chart.
2021-02-10 Renamed capture screen to osciloscope screen
2021-02-13 Added phase screen
2021-02-13 Cleaned up the phase screen.
2021-02-13 Added phase screen shots.
2021-02-13 Added documentation for the phase screen.
2021-02-13 Added a TODO
2021-02-13 Tweak capture start/stop logic.
2021-02-14 Shared capture buffer works. Code needs cleanup.
2021-02-15 Clenaed up capture util.
2021-02-15 Added capture speed control in the phase screen.
2021-02-15 Updated phase screen screenshots.
2021-02-15 Teaked phase mapping.
2021-02-15 Updated documentation.
2021-02-15 Added a third scale to the retration graph.
2021-02-16 Released a new binary.
2021-02-16 Tweaks
2021-02-16 tweak
2021-02-27 Extended the click area of buttons.
2021-02-27 Created a release binary
2021-02-27 Minor doc ttweak.
2021-03-27 Assorted tweaks.
2021-04-16 added the enclosed case option
2021-04-17 Minor doc tweaks.
2021-04-17 Added BOM.
2021-04-17 Removed the DO NOT POPULATE comment for the 10uf caps since they are populated in the prototype.
2021-04-18 Added 0.3 membrane at the back cover holes to improve 3d printing without material support. Should be drilled through with a 2.5mm (aprox 3/32" imperial).
2021-04-20 Updated BOM link.
2021-04-20 Minor doc tweak
2021-05-14 arduino camel case fix
2021-05-16 Added an errata regarding floating TFT pin 26.
2021-05-16 Updated schematic with errata
2021-06-01 Added note about the upcoming new design.
2021-06-01 Updated links (simple -> legacy)

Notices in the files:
README.md:
Q: The Analyzer uses LVGL lib, what is the license of that library?:
A: At the time of writing this, the LVGL license is available here https://github.com/lvgl/lvgl/blob/master/LICENCE.txt.  The Analyzer's developers are not affiliated with LVGL.
kicad/stepper_analyzer.kicad_pcb:
REV 1.0,  OSH CC0
